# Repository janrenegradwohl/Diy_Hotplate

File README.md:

# DIY HotPlate

I needed a reflow hot plate for reflow-soldering, so I decided to build one myself. I used an STM32F301, which is connected to the PC via a USB-UART bridge. I’ve already ordered the second revision of the hardware.

I’m currently working on the hardware and firmware. PC software for control and data plotting will follow soon.

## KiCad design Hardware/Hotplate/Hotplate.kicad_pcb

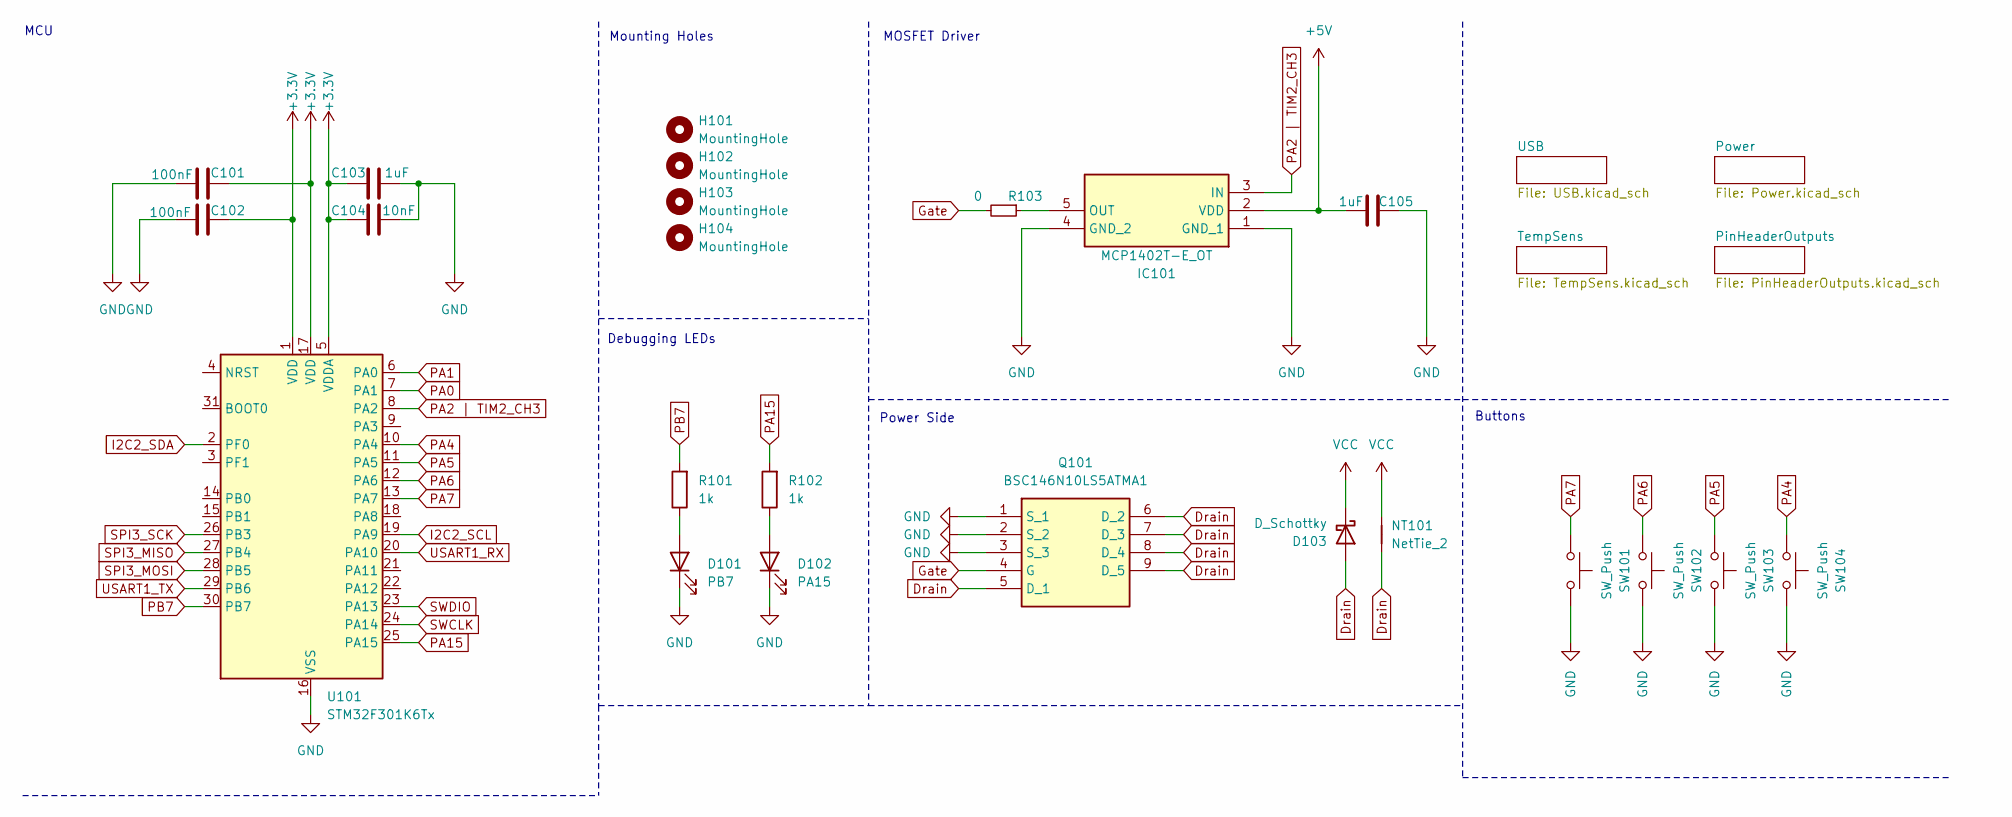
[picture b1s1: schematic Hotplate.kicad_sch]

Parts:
C101, C102: 100nF; C_0603_1608Metric
C103, C105: 1uF; C_0603_1608Metric
C104: 10nF; C_0603_1608Metric
D101: PB7; LED_0603_1608Metric_Pad1.05x0.95mm_HandSolder
D102: PA15; LED_0603_1608Metric_Pad1.05x0.95mm_HandSolder
D103: D_Schottky; D_DO-15_P10.16mm_Horizontal
H101, H102, H103, H104: MountingHole; MountingHole_2.7mm_M2.5
IC101: MCP1402T-E_OT; SOT95P270X145-5N; Mouser Part Number 579-MCP1402T-E/OT
NT101: NetTie_2; NetTie-2_SMD_Pad2.0mm
Q101: BSC146N10LS5ATMA1; Mouser Part Number 726-BSC146N10LS5ATMA
R101, R102: 1k; R_0603_1608Metric_Pad0.98x0.95mm_HandSolder
R103: 0; R_0603_1608Metric_Pad0.98x0.95mm_HandSolder
SW101, SW102, SW103, SW104: SW_Push; SW_PUSH_6mm
U101: STM32F301K6Tx; LQFP-32_7x7mm_P0.8mm

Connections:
+3.3V: C101.2, C102.2, C103.2, C104.2, U101.1 (VDD), U101.5 (VDDA), U101.17 (VDD); also elsewhere on the board
+5V: C105.2, IC101.2 (VDD); also elsewhere on the board
Drain: D103.2 (A), NT101.1, Q101.5 (D_1), Q101.6 (D_2), Q101.7 (D_3), Q101.8 (D_4), Q101.9 (D_5)
GND: C101.1, C102.1, C103.1, C104.1, C105.1, D101.1 (K), D102.1 (K), IC101.1 (GND_1), IC101.4 (GND_2), Q101.1 (S_1), Q101.2 (S_2), Q101.3 (S_3), SW101.2, SW102.2, SW103.2, SW104.2, U101.16 (VSS), U101.32 (VSS); also elsewhere on the board
Gate: Q101.4 (G), R103.2
I2C2_SCL: U101.19 (PA9); also elsewhere on the board
I2C2_SDA: U101.2 (PF0); also elsewhere on the board
unnamed: D101.2 (A), R101.1
unnamed: D102.2 (A), R102.1
unnamed: IC101.5 (OUT), R103.1
PA0: U101.7 (PA1); also elsewhere on the board
PA1: U101.6 (PA0); also elsewhere on the board
PA2 | TIM2_CH3: IC101.3 (IN), U101.8 (PA2)
PA4: SW104.1, U101.10 (PA4)
PA5: SW103.1, U101.11 (PA5)
PA6: SW102.1, U101.12 (PA6)
PA7: SW101.1, U101.13 (PA7)
PA15: R102.2, U101.25 (PA15)
PB7: R101.2, U101.30 (PB7)
SPI3_MISO: U101.27 (PB4); also elsewhere on the board
SPI3_MOSI: U101.28 (PB5); also elsewhere on the board
SPI3_SCK: U101.26 (PB3); also elsewhere on the board
SWCLK: U101.24 (PA14); also elsewhere on the board
SWDIO: U101.23 (PA13); also elsewhere on the board
USART1_RX: U101.20 (PA10); also elsewhere on the board
USART1_TX: U101.29 (PB6); also elsewhere on the board
VCC: D103.1 (K), NT101.2; also elsewhere on the board

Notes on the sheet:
MOSFET Driver
Mounting Holes
MCU
Buttons
Debugging LEDs
Power Side

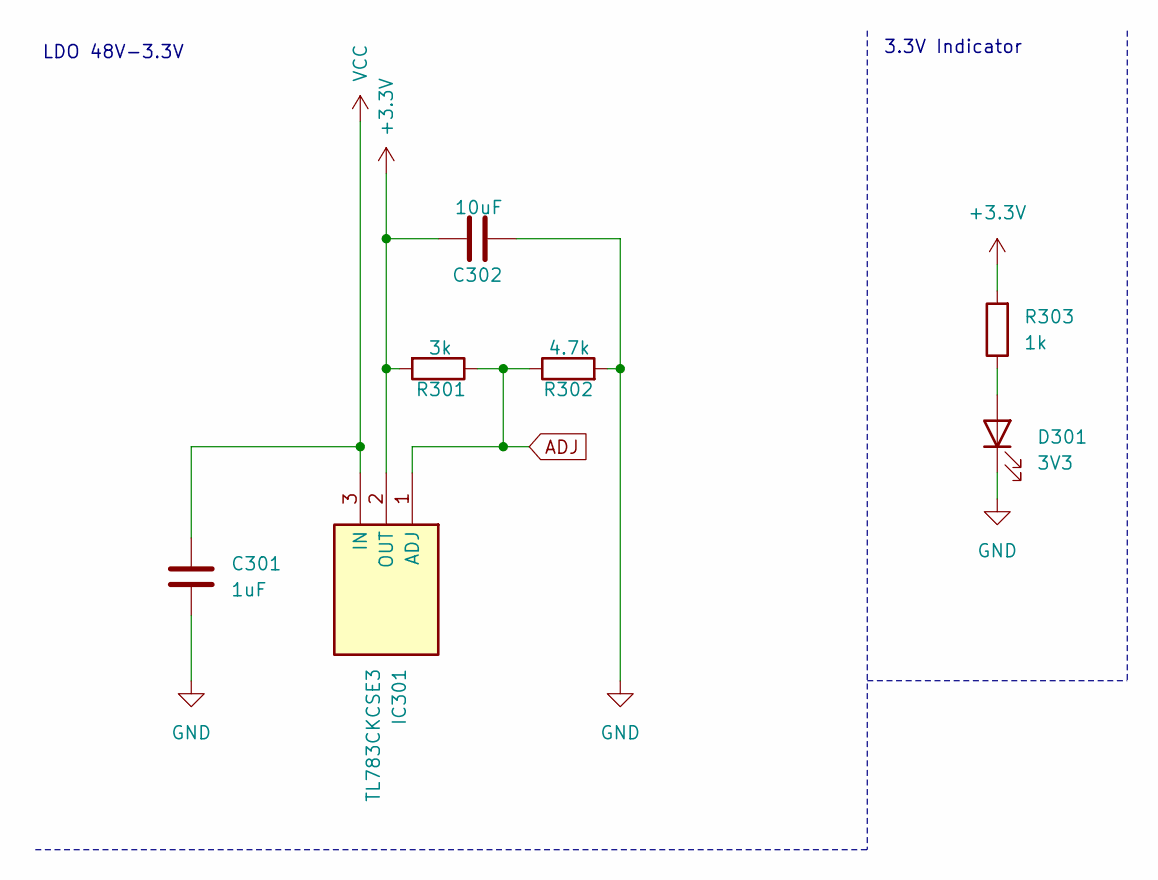
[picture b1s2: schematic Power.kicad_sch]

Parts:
C301: 1uF; C_0805_2012Metric; LCSC C15849
C302: 10uF; C_0805_2012Metric; LCSC C15849
D301: 3V3; LED_0603_1608Metric_Pad1.05x0.95mm_HandSolder
IC301: TL783CKCSE3; TO254P470X1016X1965-3P; Mouser Part Number 595-TL783CKCSE3
R301: 3k; R_0805_2012Metric
R302: 4.7k; R_0805_2012Metric
R303: 1k; R_0603_1608Metric_Pad0.98x0.95mm_HandSolder

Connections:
+3.3V: C302.2, IC301.2 (OUT), R301.2, R303.2; also elsewhere on the board
ADJ: IC301.1 (ADJ), R301.1, R302.1
GND: C301.2, C302.1, D301.1 (K), R302.2; also elsewhere on the board
unnamed: D301.2 (A), R303.1
VCC: C301.1, IC301.3 (IN); also elsewhere on the board

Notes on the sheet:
LDO 48V-3.3V
3.3V Indicator

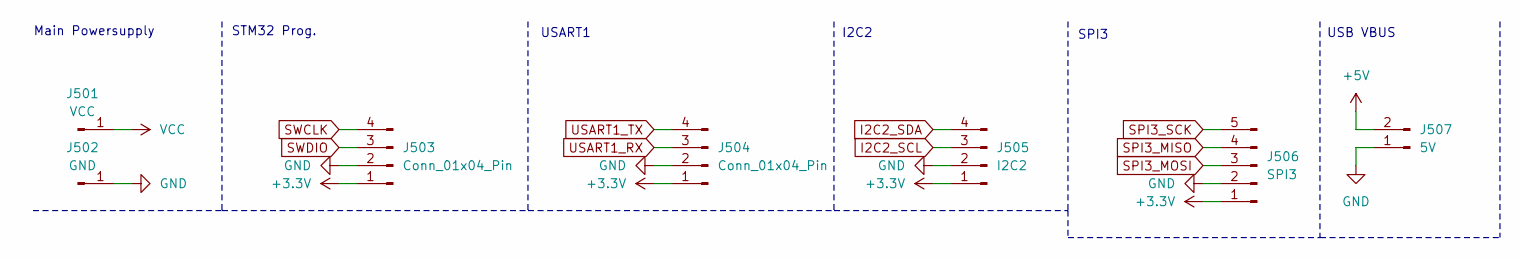
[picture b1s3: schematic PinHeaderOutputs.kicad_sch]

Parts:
J501: VCC; SolderWire-1.5sqmm_1x01_D1.7mm_OD3mm
J502: GND; SolderWire-1.5sqmm_1x01_D1.7mm_OD3mm
J503, J504: Conn_01x04_Pin; PinHeader_1x04_P2.54mm_Vertical
J505: I2C2; PinHeader_1x04_P2.54mm_Vertical
J506: SPI3; PinHeader_1x05_P2.54mm_Vertical
J507: 5V; PinHeader_1x02_P2.54mm_Vertical

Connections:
+3.3V: J503.1, J504.1, J505.1, J506.1; also elsewhere on the board
+5V: J507.2; also elsewhere on the board
GND: J502.1, J503.2, J504.2, J505.2, J506.2, J507.1; also elsewhere on the board
I2C2_SCL: J505.3; also elsewhere on the board
I2C2_SDA: J505.4; also elsewhere on the board
SPI3_MISO: J506.4; also elsewhere on the board
SPI3_MOSI: J506.3; also elsewhere on the board
SPI3_SCK: J506.5; also elsewhere on the board
SWCLK: J503.4; also elsewhere on the board
SWDIO: J503.3; also elsewhere on the board
USART1_RX: J504.3; also elsewhere on the board
USART1_TX: J504.4; also elsewhere on the board
VCC: J501.1; also elsewhere on the board

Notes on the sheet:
Main Powersupply
I2C2
SPI3
STM32 Prog.
USB VBUS
USART1

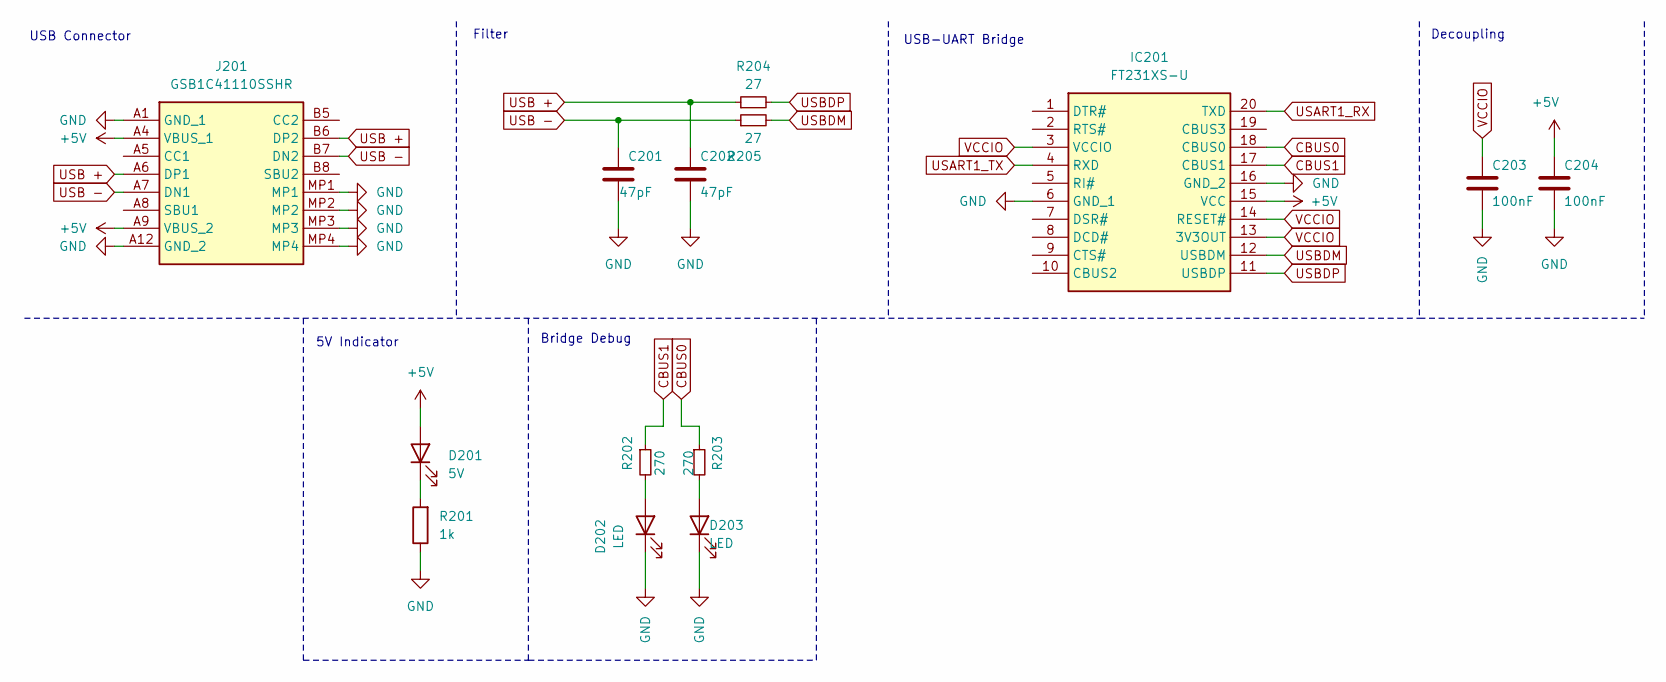
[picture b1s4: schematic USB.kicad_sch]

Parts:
C201, C202: 47pF; C_0603_1608Metric_Pad1.08x0.95mm_HandSolder
C203, C204: 100nF; C_0603_1608Metric_Pad1.08x0.95mm_HandSolder
D201: 5V; LED_0603_1608Metric_Pad1.05x0.95mm_HandSolder
D202, D203: LED; LED_0603_1608Metric_Pad1.05x0.95mm_HandSolder
IC201: FT231XS-U; SOP64P599X175-20N; Mouser Part Number 895-FT231XS-U
J201: GSB1C41110SSHR; Manufacturer_Part_Number GSB1C41110SSHR
R201: 1k; R_0603_1608Metric_Pad0.98x0.95mm_HandSolder
R202, R203: 270; R_0603_1608Metric_Pad0.98x0.95mm_HandSolder
R204, R205: 27; R_0603_1608Metric_Pad0.98x0.95mm_HandSolder

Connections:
+5V: C204.1, D201.2 (A), IC201.15 (VCC), J201.A4 (VBUS_1), J201.A9 (VBUS_2); also elsewhere on the board
CBUS0: IC201.18 (CBUS0), R203.1
CBUS1: IC201.17 (CBUS1), R202.1
GND: C201.2, C202.2, C203.2, C204.2, D202.1 (K), D203.1 (K), IC201.6 (GND_1), IC201.16 (GND_2), J201.A1 (GND_1), J201.A12 (GND_2), J201.MP1, J201.MP2, J201.MP3, J201.MP4, R201.1; also elsewhere on the board
unnamed: D201.1 (K), R201.2
unnamed: D202.2 (A), R202.2
unnamed: D203.2 (A), R203.2
USART1_RX: IC201.20 (TXD); also elsewhere on the board
USART1_TX: IC201.4 (RXD); also elsewhere on the board
USB +: C202.1, J201.A6 (DP1), J201.B6 (DP2), R204.1
USB -: C201.1, J201.A7 (DN1), J201.B7 (DN2), R205.1
USBDM: IC201.12 (USBDM), R205.2
USBDP: IC201.11 (USBDP), R204.2
VCCIO: C203.1, IC201.3 (VCCIO), IC201.13 (3V3OUT), IC201.14 (RESET#)

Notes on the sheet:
Filter
USB-UART Bridge
Bridge Debug
Decoupling
USB Connector
5V Indicator

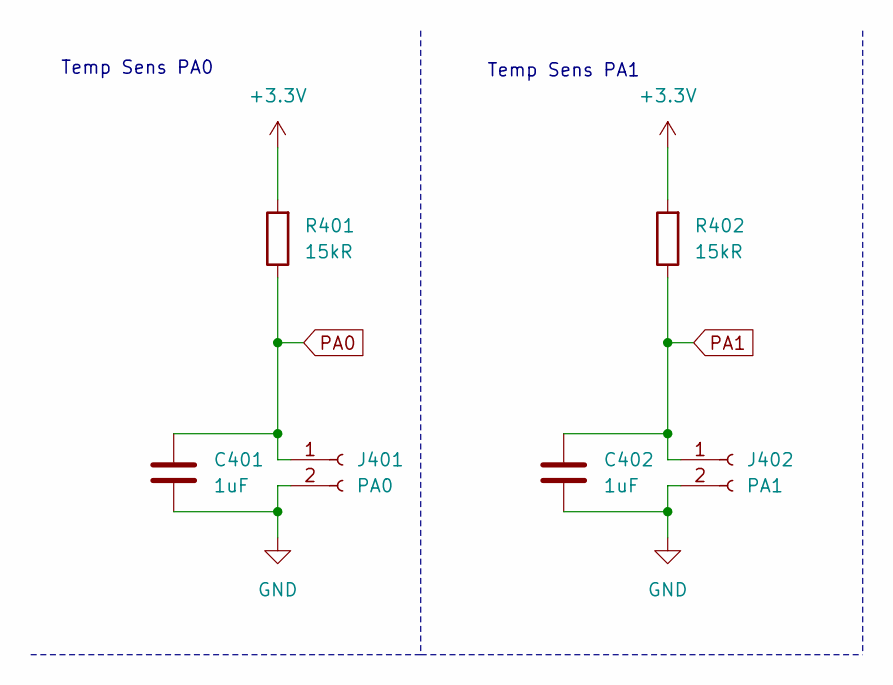
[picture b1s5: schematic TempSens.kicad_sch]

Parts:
C401, C402: 1uF; C_0603_1608Metric; LCSC C15849
J401: PA0; JST_EH_B2B-EH-A_1x02_P2.50mm_Vertical
J402: PA1; JST_EH_B2B-EH-A_1x02_P2.50mm_Vertical
R401, R402: 15kR; R_0805_2012Metric; LCSC C17475

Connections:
+3.3V: R401.2, R402.2; also elsewhere on the board
GND: C401.2, C402.2, J401.2, J402.2; also elsewhere on the board
PA0: C401.1, J401.1, R401.1; also elsewhere on the board
PA1: C402.1, J402.1, R402.1; also elsewhere on the board

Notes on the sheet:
Temp Sens PA1
Temp Sens PA0

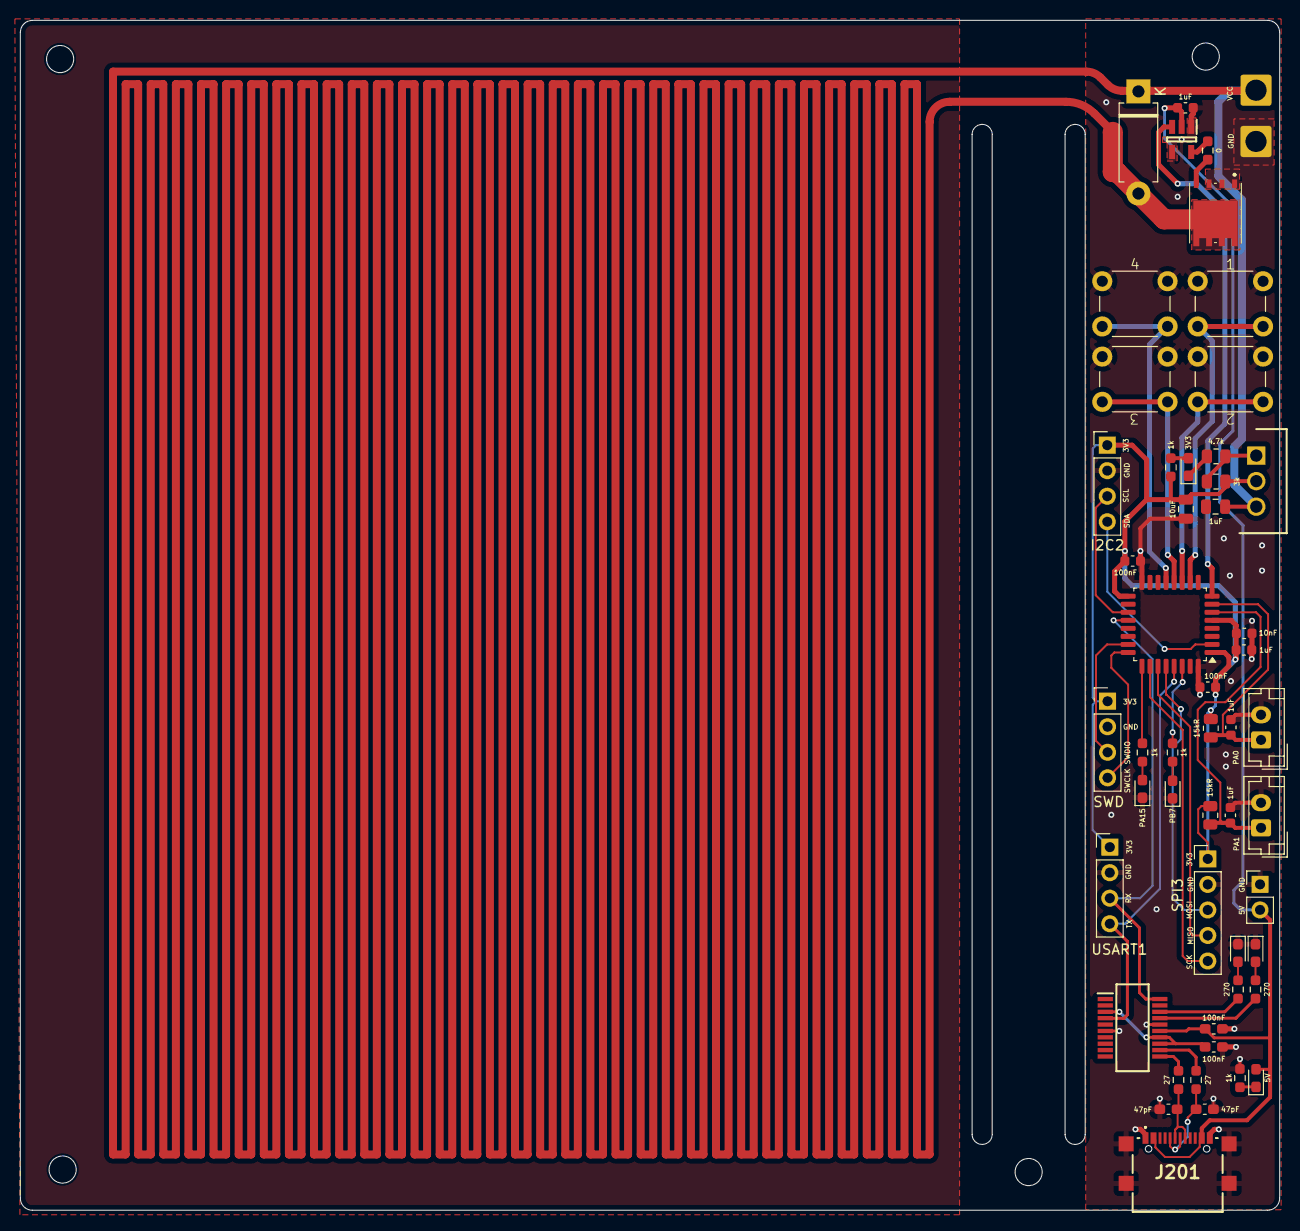
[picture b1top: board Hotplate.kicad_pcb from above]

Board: 2 copper layers, 125.3 x 118.4 mm, 57 parts (0 on the bottom side), 39 nets.

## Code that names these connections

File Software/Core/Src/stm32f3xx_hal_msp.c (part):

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
    __HAL_RCC_GPIOA_CLK_ENABLE();
    /**ADC1 GPIO Configuration
    PA0     ------> ADC1_IN1
    PA1     ------> ADC1_IN2
    */
    GPIO_InitStruct.Pin = GPIO_PIN_0|GPIO_PIN_1;
    GPIO_InitStruct.Mode = GPIO_MODE_ANALOG;
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    __HAL_RCC_ADC1_CLK_DISABLE();

    /**ADC1 GPIO Configuration
    PA0     ------> ADC1_IN1
    PA1     ------> ADC1_IN2
    */
    HAL_GPIO_DeInit(GPIOA, GPIO_PIN_0|GPIO_PIN_1);

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    __HAL_RCC_GPIOF_CLK_ENABLE();
    __HAL_RCC_GPIOA_CLK_ENABLE();
    /**I2C2 GPIO Configuration
    PF0-OSC_IN     ------> I2C2_SDA
    PA9     ------> I2C2_SCL
    */
    GPIO_InitStruct.Pin = GPIO_PIN_0;
    GPIO_InitStruct.Mode = GPIO_MODE_AF_OD;
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    __HAL_RCC_I2C2_CLK_DISABLE();

    /**I2C2 GPIO Configuration
    PF0-OSC_IN     ------> I2C2_SDA
    PA9     ------> I2C2_SCL
    */
    HAL_GPIO_DeInit(GPIOF, GPIO_PIN_0);

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
    __HAL_RCC_GPIOB_CLK_ENABLE();
    /**SPI3 GPIO Configuration
    PB3     ------> SPI3_SCK
    PB4     ------> SPI3_MISO
    PB5     ------> SPI3_MOSI
    */
    GPIO_InitStruct.Pin = GPIO_PIN_3|GPIO_PIN_4|GPIO_PIN_5;
    GPIO_InitStruct.Mode = GPIO_MODE_AF_PP;
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    __HAL_RCC_SPI3_CLK_DISABLE();

    /**SPI3 GPIO Configuration
    PB3     ------> SPI3_SCK
    PB4     ------> SPI3_MISO
    PB5     ------> SPI3_MOSI
    */
    HAL_GPIO_DeInit(GPIOB, GPIO_PIN_3|GPIO_PIN_4|GPIO_PIN_5);

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
    __HAL_RCC_GPIOA_CLK_ENABLE();
    /**TIM2 GPIO Configuration
    PA2     ------> TIM2_CH3
    */
    GPIO_InitStruct.Pin = GPIO_PIN_2;
    GPIO_InitStruct.Mode = GPIO_MODE_AF_PP;
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    __HAL_RCC_GPIOA_CLK_ENABLE();
    __HAL_RCC_GPIOB_CLK_ENABLE();
    /**USART1 GPIO Configuration
    PA10     ------> USART1_RX
    PB6     ------> USART1_TX
    */
    GPIO_InitStruct.Pin = GPIO_PIN_10;
    GPIO_InitStruct.Mode = GPIO_MODE_AF_PP;
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    __HAL_RCC_USART1_CLK_DISABLE();

    /**USART1 GPIO Configuration
    PA10     ------> USART1_RX
    PB6     ------> USART1_TX
    */
    HAL_GPIO_DeInit(GPIOA, GPIO_PIN_10);

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
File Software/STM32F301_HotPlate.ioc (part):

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Mcu.Name=STM32F301K(6-8)Tx
Mcu.Package=LQFP32
Mcu.UserName=STM32F301K6Tx
PA0.Mode=IN1-Single-Ended
PA0.Signal=ADC1_IN1
PA1.Mode=IN2-Single-Ended
PA1.Signal=ADC1_IN2
PA10.Mode=Asynchronous
PA10.Signal=USART1_RX
PA13.Mode=Serial_Wire
PA13.Signal=SYS_JTMS-SWDIO
PA14.Mode=Serial_Wire
PA14.Signal=SYS_JTCK-SWCLK
PA15.GPIOParameters=GPIO_Label
PA15.GPIO_Label=D6
PA15.Signal=GPIO_Output
PA2.Signal=S_TIM2_CH3
PA4.GPIOParameters=GPIO_Label
PA4.GPIO_Label=B1
PA4.Signal=GPIO_Output
PA5.GPIOParameters=GPIO_Label
PA5.GPIO_Label=B2
PA5.Signal=GPIO_Output
PA6.GPIOParameters=GPIO_Label
PA6.GPIO_Label=B3
PA6.Signal=GPIO_Input
PA7.GPIOParameters=GPIO_Label
PA7.GPIO_Label=B4
PA7.Signal=GPIO_Input
PB6.Mode=Asynchronous
PB6.Signal=USART1_TX
PB7.GPIOParameters=GPIO_Label
PB7.GPIO_Label=D5
PB7.Signal=GPIO_Output
RCC.HSEPLLFreq_Value=8000000
RCC.HSE_VALUE=8000000
RCC.SYSCLKFreq_VALUE=64000000
RCC.SYSCLKSourceVirtual=RCC_SYSCLKSOURCE_PLLCLK
board=custom

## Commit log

2026-02-15 Initialize README with project details
    Added project description for DIY HotPlate.
2026-02-17 Tested PCB V2
2026-02-17 Deleted PCB BackUps
2026-02-19 Debuging Code
2026-02-19 Tested FT231
2026-02-19 Added FT_Prog picture
2026-02-24 Updated Kicad 8 to 9
2026-03-03 Update?
2026-03-03 fixed USB connection
2026-03-03 added Timer
2026-03-03 added Timer (#7)
2026-03-10 made it pretty
2026-03-10 made it pretty (#8)
2026-03-10 debugged, tim6 error
2026-03-10 debugged, tim6 error (#9)
2026-03-17 fixed tim6
2026-03-17 fixed tim6 (#10)
2026-03-24 Debbuged, tempsense error
2026-03-24 Debbuged, tempsense error (#11)
2026-04-07 fixed:ADC reading
2026-04-07 fixed:ADC reading (#12)
2026-04-08 fixed:flashsize(buildinrelease), fixed:tim6, fixed:tim1
2026-04-08 fixed:flashsize(buildinrelease), fixed:tim6, fixed:tim1 (#13)
2026-04-15 error: PID
2026-04-15 error: PID (#14)
2026-04-19 fixed:PID
2026-04-19 fixed:dyingFETs
2026-04-19 Debug (#15)
    * fixed:PID
    * fixed:PID
    * fixed:dyingFETs
2026-04-23 Debugged: FETDriver too slow
2026-04-23 Debugged: FETDriver too slow (#16)

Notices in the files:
Software/Core/Src/stm32f3xx_hal_msp.c:
Copyright (c) 2025 STMicroelectronics.
All rights reserved.
This software is licensed under terms that can be found in the LICENSE file
